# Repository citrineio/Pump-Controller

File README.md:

# Pump-Controller
This is the next version of the previously featured AC Switch. This is an IOT device that can turn normal water pumps smart. This device is meant to detect plumbing issues and automatically or allow the user to act. 

## Features

 1. A wireless microcontroller (ESP32-C3-WROOM-02-N4) for remote monitoring and control of the pump.
 2.  40A SPDT relay with Quick Connect contacts (AZ2100-1CE-5DEF).
 3. 20A current transformer (ZMCT102) to detect when the pump is on by measuring motor current.
 4. A JST connector (B4B-PH-K) for a [pressure sensor](https://www.digikey.com/en/products/detail/seeed-technology-co-ltd/114991178/7387419)  to identify if the pump is pumping air.
 5. An AC/DC converter (PBO-5C-5 or equivalent) to supply power from an outlet.

## Block Diagram

## Future improvements

 1. Replace spring clamp terminal blocks with pluggable or screw terminals.
 2. Replace the JST connector with a pluggable terminal block.
 3. Replace TC2050 footprint and UART JST connector with 2.54mm footprints for use with a pogo pin probe clip (e.g. [This](https://www.adafruit.com/product/5434)).
 4. The board was designed with a specific enclosure in mind. Future revisions will have their own custom designed enclosure.
 5. Tagconnect cables without clamps are very inconvenient. 

Please let me know if you have any suggestions or improvements

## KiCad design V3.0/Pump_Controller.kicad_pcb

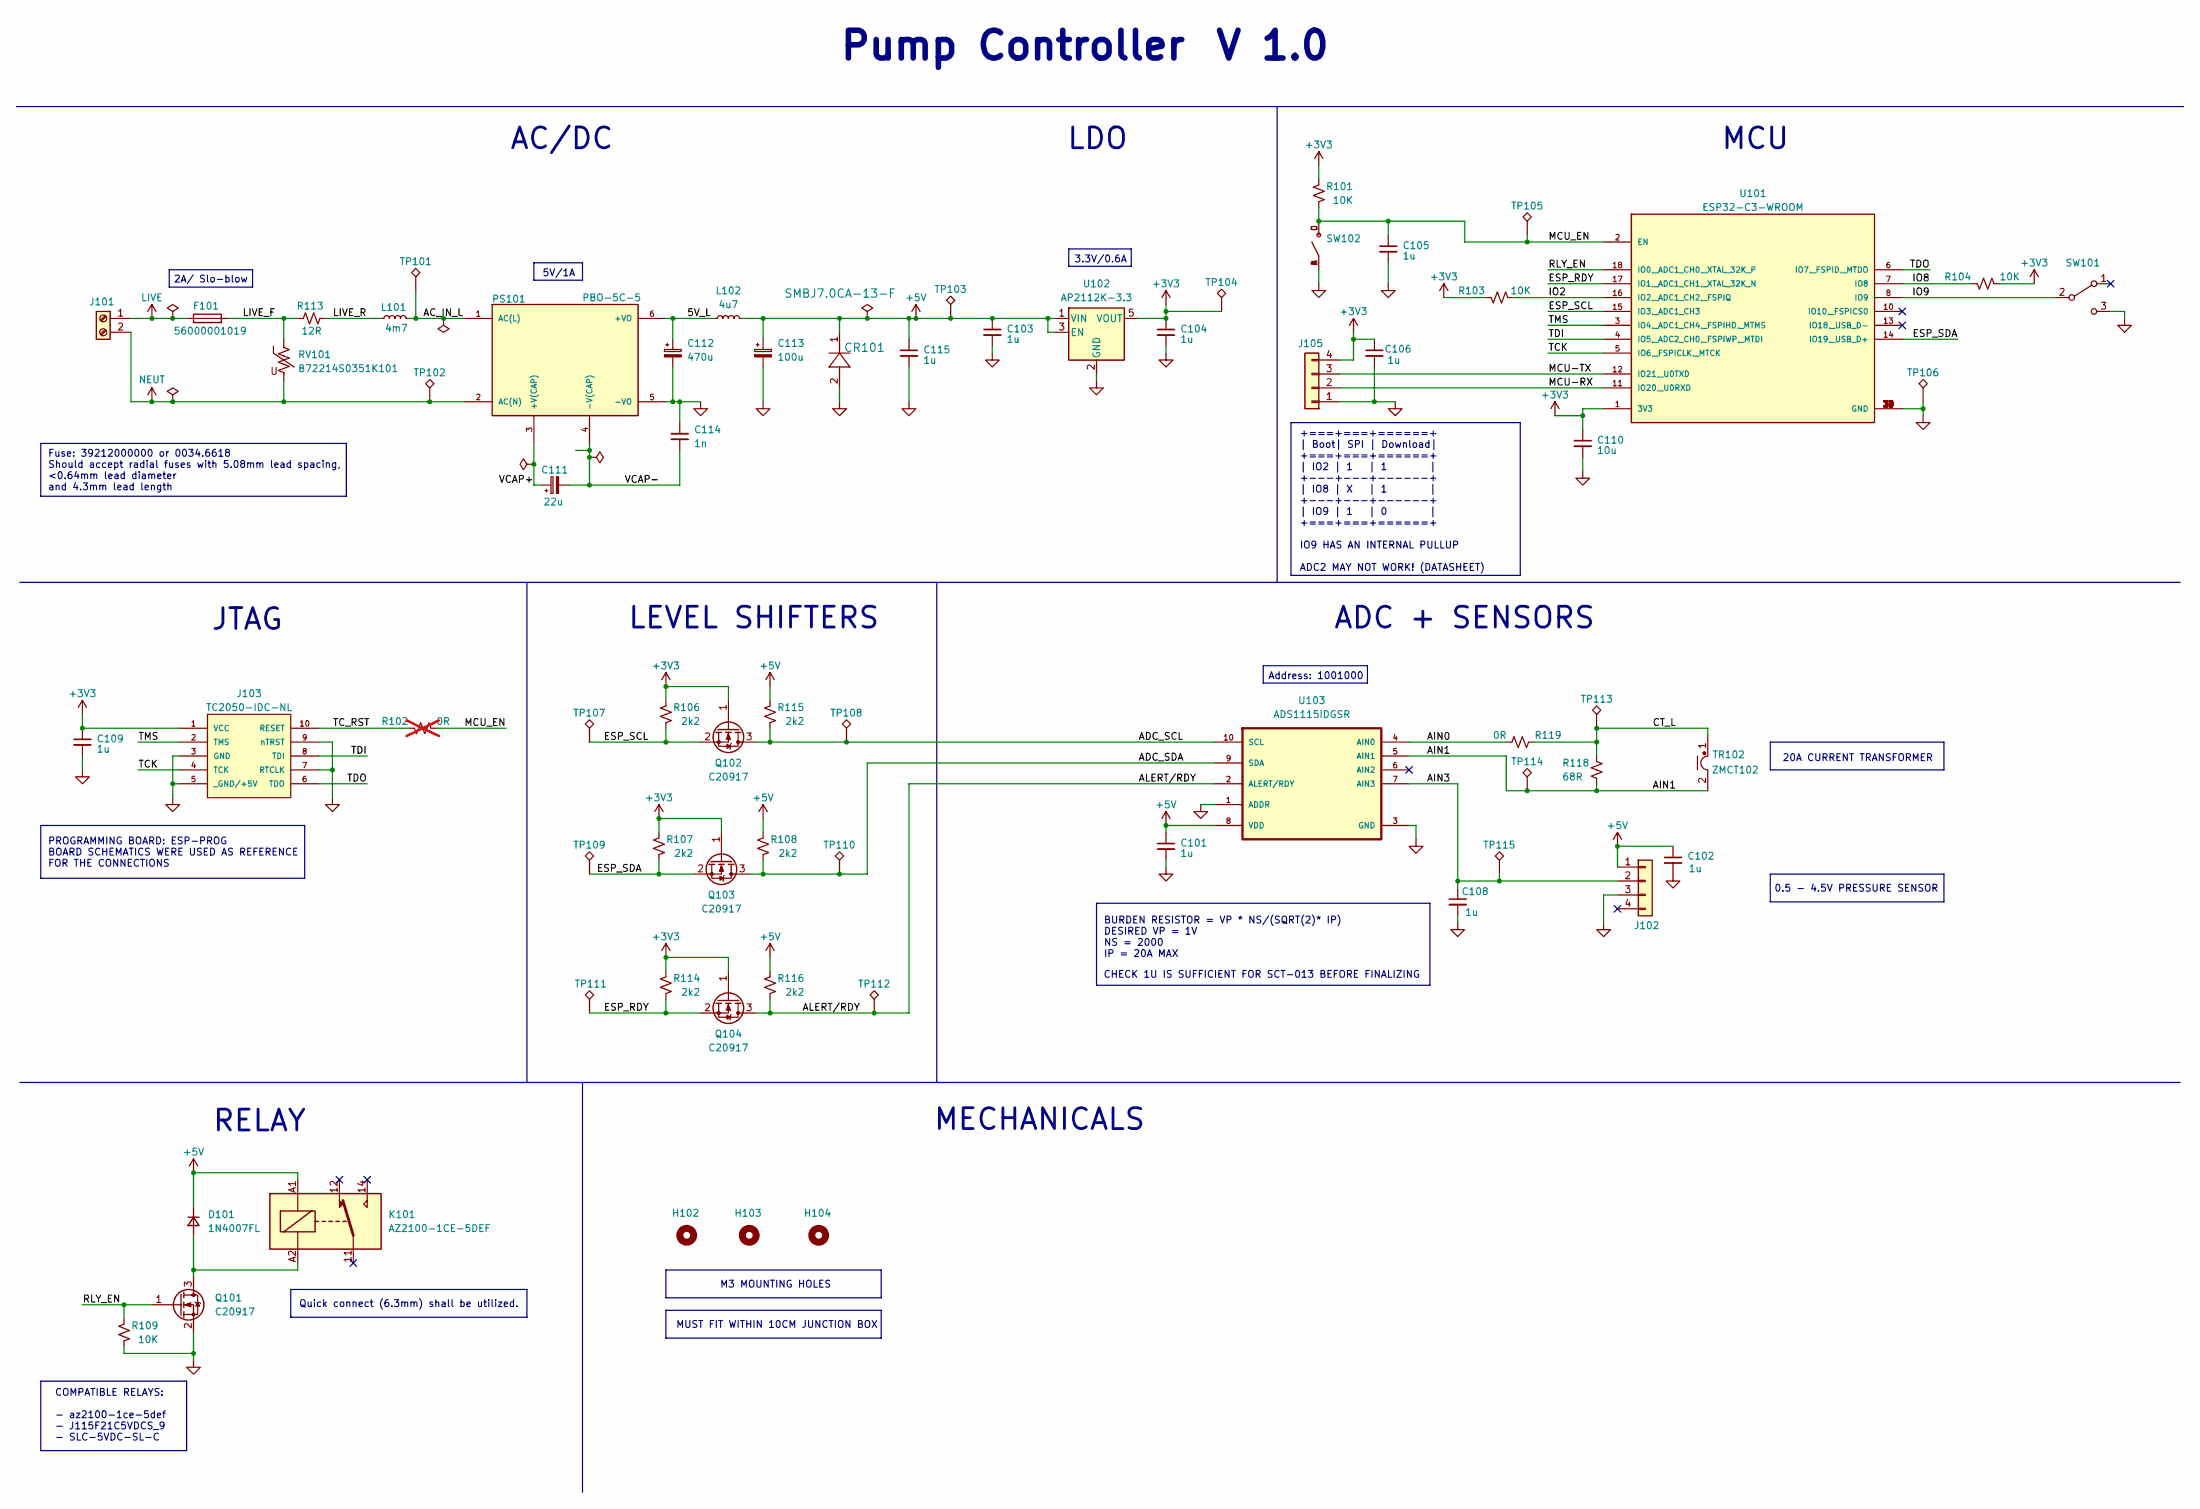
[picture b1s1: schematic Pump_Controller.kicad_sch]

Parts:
C101, C102, C103, C104, C105, C106, C108, C109, C115: 1u; CL10A; Part Number CL10B105KO8NNNC - C59782
C110: 10u; CL10A; Part Number CL10A106MA8NRNC - C96446
C111: 22u; CP_Radial_D12.5mm_P5.00mm; Part Number B43821F5226M000
C112: 470u; CP_Radial_D6.3mm_P2.50mm; Part Number A750EQ477M1CAAE015
C113: 100u; CP_Radial_D6.3mm_P2.50mm; Part Number ESL107M035AE3AA
C114: 1n; CAP_CL31_SAM; Part Number CL31B102KHFNFNE
CR101: SMBJ7.0CA-13-F; SMB_DIO; Part Number SMBJ7.0CA-13-F
D101: 1N4007FL; SODFL3618X110N; Part Number 1N4007FL
F101: 56000001019; FUSE_560_1019_LTF; Part Number 56000001019
H102, H103, H104: MountingHole; MountingHole_3.2mm_M3
J101: Screw_Terminal_01x02; CONN-TH_2P-P5.08_WJ142V-5.08-2P
J102, J105: B4B-PH-K; JST_B4B-PH-K; Part Number B4B-PH-K
J103: TC2050-IDC-NL; TAG-CONNECT_TC2050-IDC-NL
K101: AZ2100-1CE-5DEF; Part Number AZ2100-1CE-5DEF
L101: 4m7; IND_RLB9012-472KL; Part Number RLB9012-472KL
L102: 4u7; IND_HL4R7M_TAY; Part Number LSXBD6060WHL4R7M
PS101: PBO-5C-5; CONV_PBO-5C-5; Part Number PBO-5C-5
Q101, Q102, Q103, Q104: C20917; SOT-23; Part Number AO3400A
R101, R103, R104, R109: 10K; RESC1607X60N; Part Number 0603WAF1002T5E - C25804
R102: 0R; RESC1607X60N; Part Number 0603WAF0000T5E - C21189; not fitted
R106, R107, R108, R114, R115, R116: 2k2; RESC1607X60N; Part Number 0603WAF2201T5E- C4190
R113: 12R; YAG_FMP200_YAG; Part Number FMP200JR-52-12R
R118: 68R; RESC1607X60N; Part Number 0603WAF680JT5E- C27592
R119: 0R; RESC1607X60N; Part Number 0603WAF0000T5E - C21189
RV101: B72214S0351K101; VAR_B72214S0351K101; Part Number B72214S0351K101
SW101: SW_SPDT; SS12D10L3; Part Number SS-12D10L3
SW102: TS-1187A-B-A-B; SW_TS-1187A-B-A-B; Part Number TS-1187A-B-A-B
TP101, TP102: TestPoint_Alt; TestPoint_Loop_D2.50mm_Drill1.0mm
TP103, TP104, TP105, TP106, TP107, TP108, TP109, TP110, TP111, TP112, TP113, TP114, TP115: TestPoint_Alt; TestPoint_Pad_1.5x1.5mm
TR102: ZMCT102; zmct102; Part Number ZMCT102
U101: ESP32-C3-WROOM; XCVR_ESP32-C3-WROOM-02U-N4; Part Number ESP32-C3-WROOM-02-N4
U102: AP2112K-3.3; SOT95P285X140-5N; Part Number AP2112K-3.3
U103: ADS1115IDGSR; ADS1115_SOP50P490X110-10N; Part Number ADS1115IDGSR

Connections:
+3V3: C104.1, C106.1, C109.1, C110.1, J103.1 (VCC), J105.4, Q102.1 (G), Q103.1 (G), Q104.1 (G), R101.1, R103.1, R104.2, R106.1, R107.1, R114.1, TP104.1, U101.1 (3V3), U102.5 (VOUT)
+5V: C101.1, C102.1, C103.1, C113.1, C115.1, CR101.1, D101.1 (K), J102.1, K101.A1, L102.2, R108.1, R115.1, R116.1, TP103.1, U102.1 (VIN), U102.3 (EN), U103.8 (VDD)
/5V_L: C112.1, L102.1, PS101.6 (+VO)
/AC_IN_L: L101.2, PS101.1 (AC(L)), TP101.1
/ADC_SCL: Q102.3 (D), R115.2, TP108.1, U103.10 (SCL)
/ADC_SDA: Q103.3 (D), R108.2, TP110.1, U103.9 (SDA)
/AIN0: R119.2, U103.4 (AIN0)
/AIN1: R118.2, TP114.1, TR102.2, U103.5 (AIN1)
/AIN3: C108.1, J102.2, TP115.1, U103.7 (AIN3)
/ALERT/RDY: Q104.3 (D), R116.2, TP112.1, U103.2 (ALERT/RDY)
/CT_L: R118.1, R119.1, TP113.1, TR102.1
/ESP_RDY: Q104.2 (S), R114.2, TP111.1, U101.17 (IO1,_ADC1_CH1,_XTAL_32K_N)
/ESP_SCL: Q102.2 (S), R106.2, TP107.1, U101.15 (IO3,_ADC1_CH3)
/ESP_SDA: Q103.2 (S), R107.2, TP109.1, U101.14 (IO19,_USB_D+)
/IO2: R103.2, U101.16 (IO2,_ADC1_CH2,_FSPIQ)
/IO8: R104.1, U101.7 (IO8)
/IO9: SW101.2 (B), U101.8 (IO9)
/LIVE_F: F101.2, R113.1, RV101.1
/LIVE_R: L101.1, R113.2
/MCU-RX: J105.2, U101.11 (IO20,_U0RXD)
/MCU-TX: J105.3, U101.12 (IO21,_U0TXD)
/MCU_EN: C105.1, R101.2, R102.2, SW102.C, SW102.D, TP105.1, U101.2 (EN)
/RLY_EN: Q101.1 (G), R109.1, U101.18 (IO0,_ADC1_CH0,_XTAL_32K_P)
/TCK: J103.4 (TCK), U101.5 (IO6,_FSPICLK,_MTCK)
/TC_RST: J103.10 (RESET), R102.1
/TDI: J103.8 (TDI), U101.4 (IO5,_ADC2_CH0,_FSPIWP,_MTDI)
/TDO: J103.6 (TDO), U101.6 (IO7,_FSPID,_MTDO)
/TMS: J103.2 (TMS), U101.3 (IO4,_ADC1_CH4,_FSPIHD,_MTMS)
/VCAP+: C111.1, PS101.3 (+V(CAP))
/VCAP-: C111.2, C114.2, PS101.4 (-V(CAP))
GND: C101.2, C102.2, C103.2, C104.2, C105.2, C106.2, C108.2, C109.2, C110.2, C112.2, C113.2, C114.1, C115.2, CR101.2, J102.3, J103.3 (GND), J103.5 (_GND/+5V), J103.7 (RTCLK), J103.9 (nTRST), J105.1, PS101.5 (-VO), Q101.2 (S), R109.2, SW101.3 (C), SW102.A, SW102.B, TP106.1, U101.9 (GND), U101.19 (GND), U101.20 (GND), U101.21 (GND), U101.22 (GND), U101.23 (GND), U101.24 (GND), U101.25 (GND), U101.26 (GND), U101.27 (GND), U101.28 (GND), U101.29 (GND), U101.30 (GND), U101.31 (GND), U101.32 (GND), U101.33 (GND), U101.34 (GND), U101.35 (GND), U101.36 (GND), U101.37 (GND), U101.38 (GND), U101.39 (GND), U102.2 (GND), U103.1 (ADDR), U103.3 (GND)
LIVE: F101.1, J101.1
NEUT: J101.2, PS101.2 (AC(N)), RV101.2, TP102.1
unnamed: D101.2 (A), K101.A2, Q101.3 (D)

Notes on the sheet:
+===+===+======+ | Boot| SPI | Download| +===+===+======+ | IO2 | 1 | 1 | +---+---+------+ | IO8 | X | 1 | +---+---+------+ | IO9 | 1 | 0 | +===+===+======+ IO9 HAS AN INTERNAL PULLUP ADC2 MAY NOT WORK! (DATASHEET)
5V/1A
0.5 - 4.5V PRESSURE SENSOR
LEVEL SHIFTERS
Quick connect (6.3mm) shall be utilized.
3.3V/0.6A
AC/DC
MUST FIT WITHIN 10CM JUNCTION BOX
RELAY
COMPATIBLE RELAYS: - az2100-1ce-5def - J115F21C5VDCS_9 - SLC-5VDC-SL-C
BURDEN RESISTOR = VP * NS/(SQRT(2)* IP) DESIRED VP = 1V NS = 2000 IP = 20A MAX
PROGRAMMING BOARD: ESP-PROG BOARD SCHEMATICS WERE USED AS REFERENCE FOR THE CONNECTIONS
JTAG
M3 MOUNTING HOLES
20A CURRENT TRANSFORMER
Pump Controller
LDO
Fuse: 39212000000 or 0034.6618 Should accept radial fuses with 5.08mm lead spacing, <0.64mm lead diameter and 4.3mm lead length
Address: 1001000
CHECK 1U IS SUFFICIENT FOR SCT-013 BEFORE FINALIZING
MECHANICALS
2A/ Slo-blow
MCU
ADC + SENSORS
V 1.0

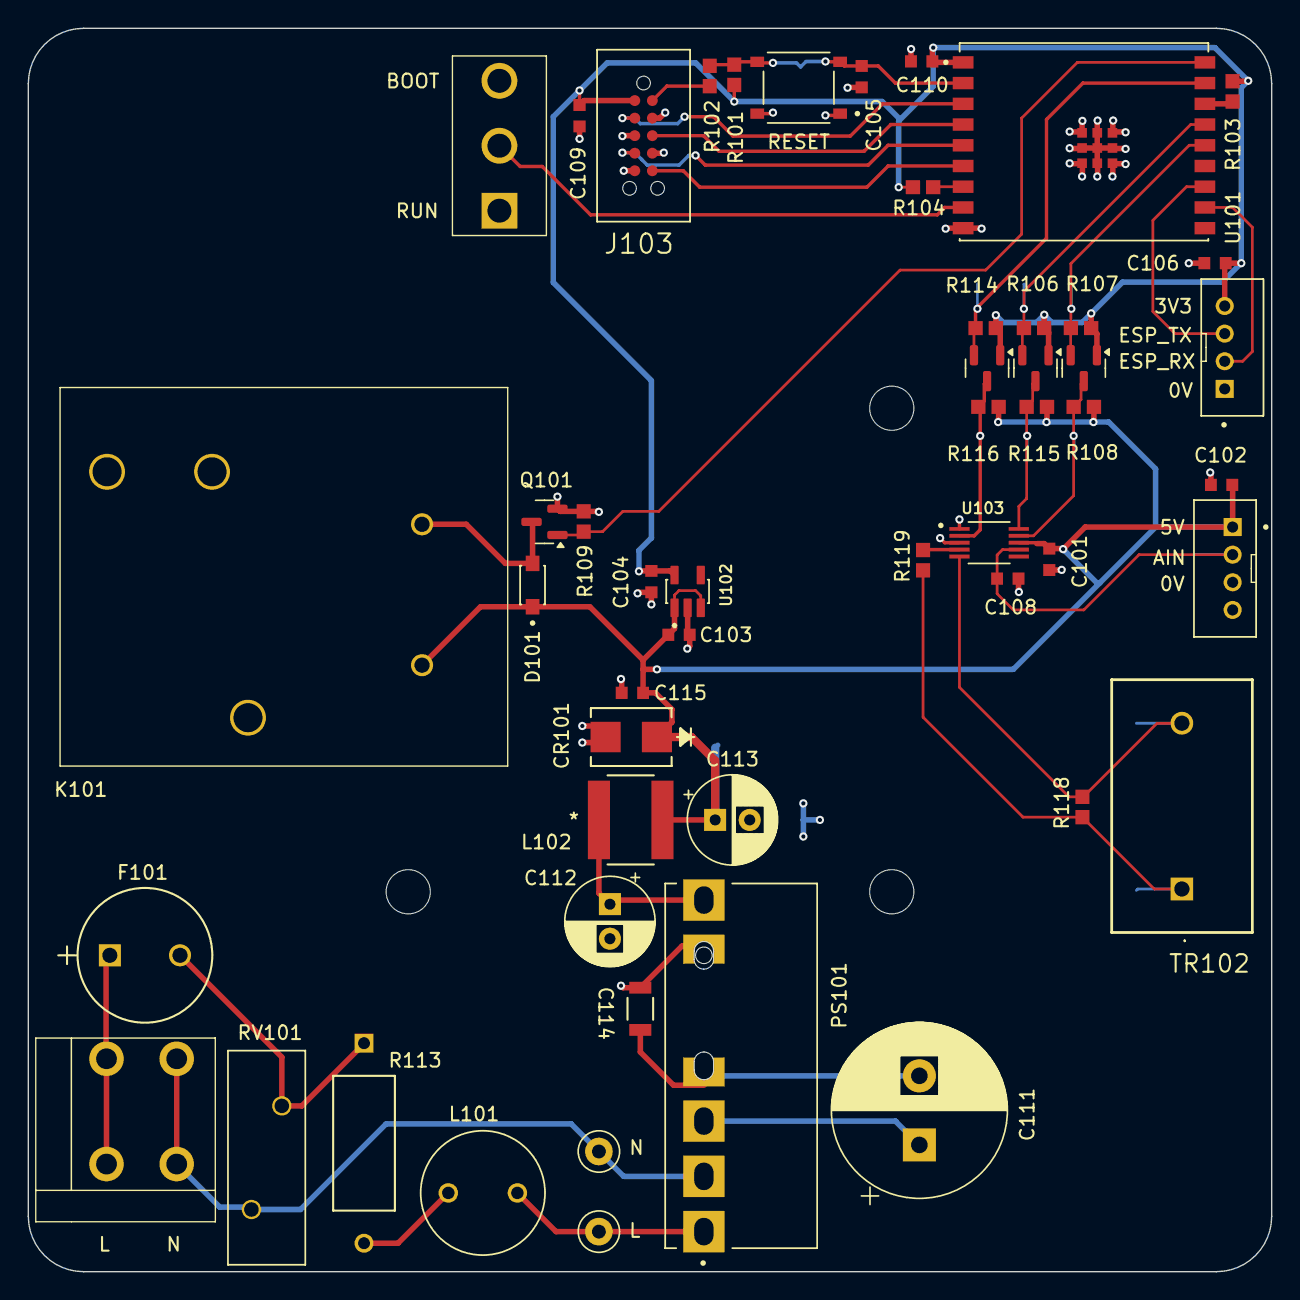
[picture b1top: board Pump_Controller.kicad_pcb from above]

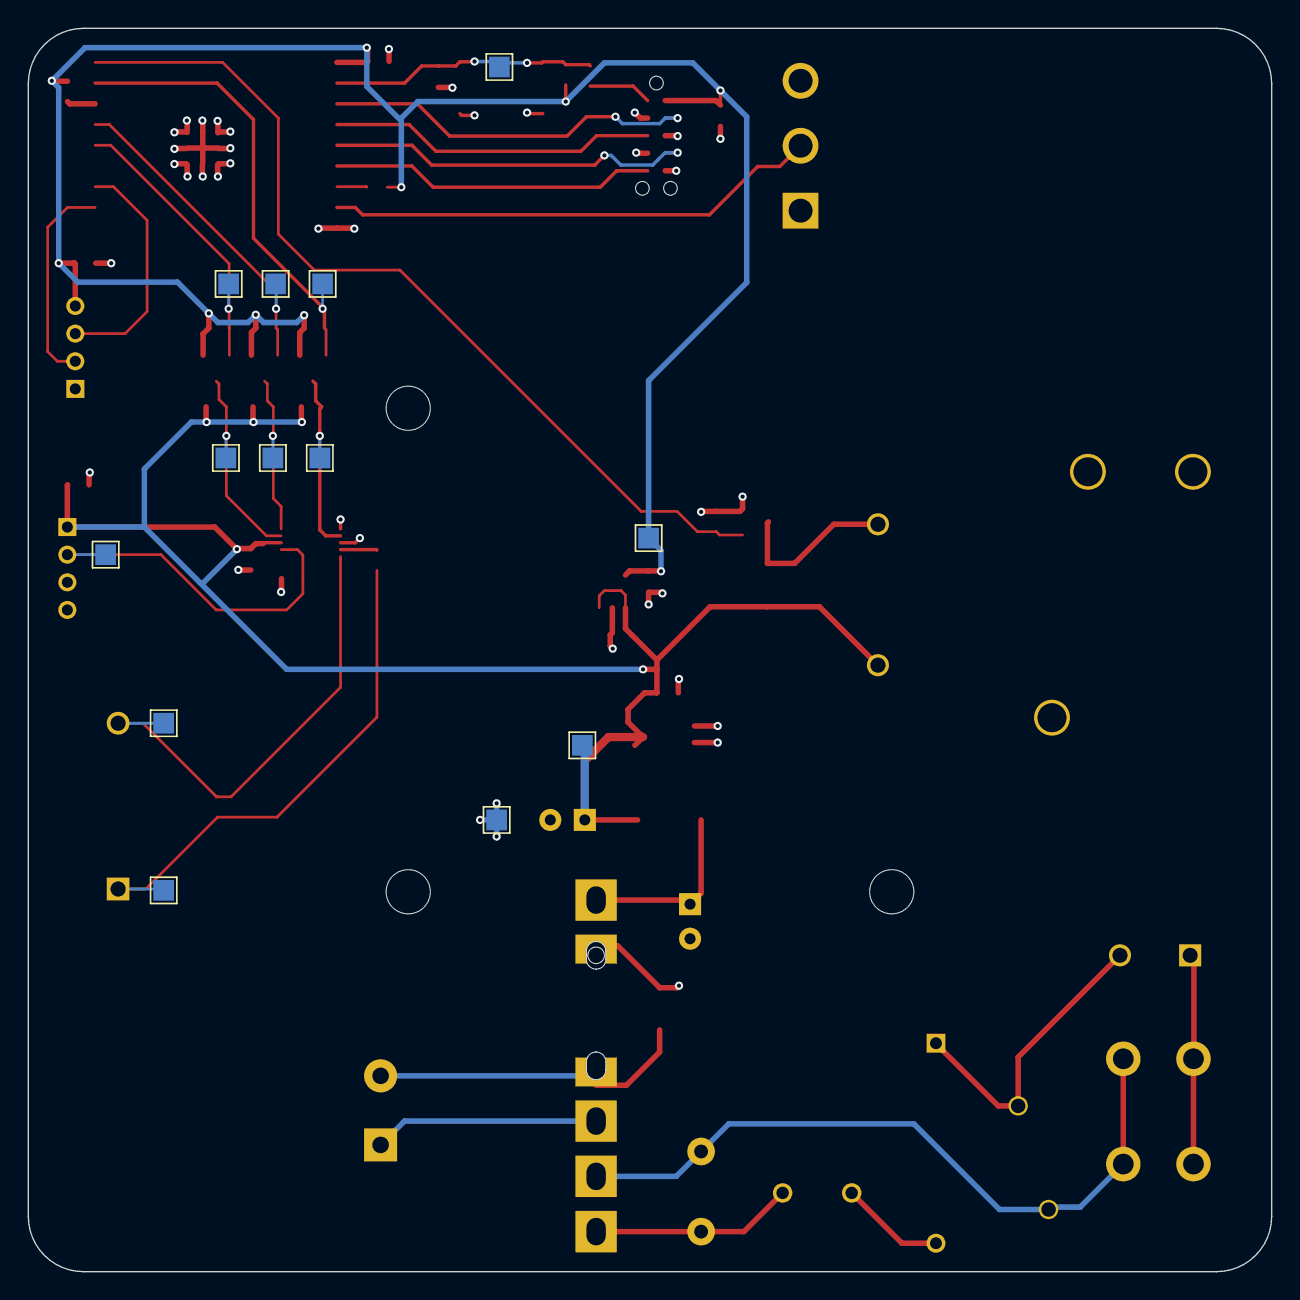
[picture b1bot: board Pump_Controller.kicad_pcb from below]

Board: 4 copper layers, 90.0 x 90.0 mm, 68 parts (13 on the bottom side), 34 nets.

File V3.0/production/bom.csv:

Designator,Footprint,Quantity,Value,LCSC Part #
"C101, C102, C103, C104, C105, C106, C108, C109, C115",CL10A,9,1u,
C110,CL10A,1,10u,
C111,CP_Radial_D12.5mm_P5.00mm,1,22u,
C112,CP_Radial_D6.3mm_P2.50mm,1,470u,
C113,CP_Radial_D6.3mm_P2.50mm,1,100u,
C114,CAP_CL31_SAM,1,1n,
CR101,SMB_DIO,1,SMBJ7.0CA-13-F,
D101,SODFL3618X110N,1,1N4007FL,
F101,FUSE_560_1019_LTF,1,56000001019 ,
"H102, H103, H104",MountingHole_3.2mm_M3,3,MountingHole,
J101,CONN-TH_2P-P5.08_WJ142V-5.08-2P,1,Screw_Terminal_01x02,
"J102, J105",JST_B4B-PH-K,2,B4B-PH-K,
J103,TAG-CONNECT_TC2050-IDC-NL,1,TC2050-IDC-NL,
K101,AZ2100-1CE-5DEF,1,AZ2100-1CE-5DEF,
L101,IND_RLB9012-472KL,1,4m7,
L102,IND_HL4R7M_TAY,1,4u7,
PS101,CONV_PBO-5C-5,1,PBO-5C-5,
"Q101, Q102, Q103, Q104",SOT-23,4,DMG2302UK,
"R101, R103, R104, R109",RESC1607X60N,4,10K,
"R102, R119",RESC1607X60N,2,0R,
"R106, R107, R108, R114, R115, R116",RESC1607X60N,6,2k2,
R113,YAG_FMP200_YAG,1,12R,
R118,RESC1607X60N,1,68R,
RV101,VAR_B72214S0351K101,1,B72214S0351K101,
SW101,SS12D10L3,1,SW_SPDT,
SW102,SW_TS-1187A-B-A-B,1,TS-1187A-B-A-B,
TR102,zmct102,1,ZMCT102,
U101,XCVR_ESP32-C3-WROOM-02U-N4,1,ESP32-C3-WROOM,
U102,SOT95P285X140-5N,1,AP2112K-3.3,
U103,ADS1115_SOP50P490X110-10N,1,ADS1115IDGSR,
